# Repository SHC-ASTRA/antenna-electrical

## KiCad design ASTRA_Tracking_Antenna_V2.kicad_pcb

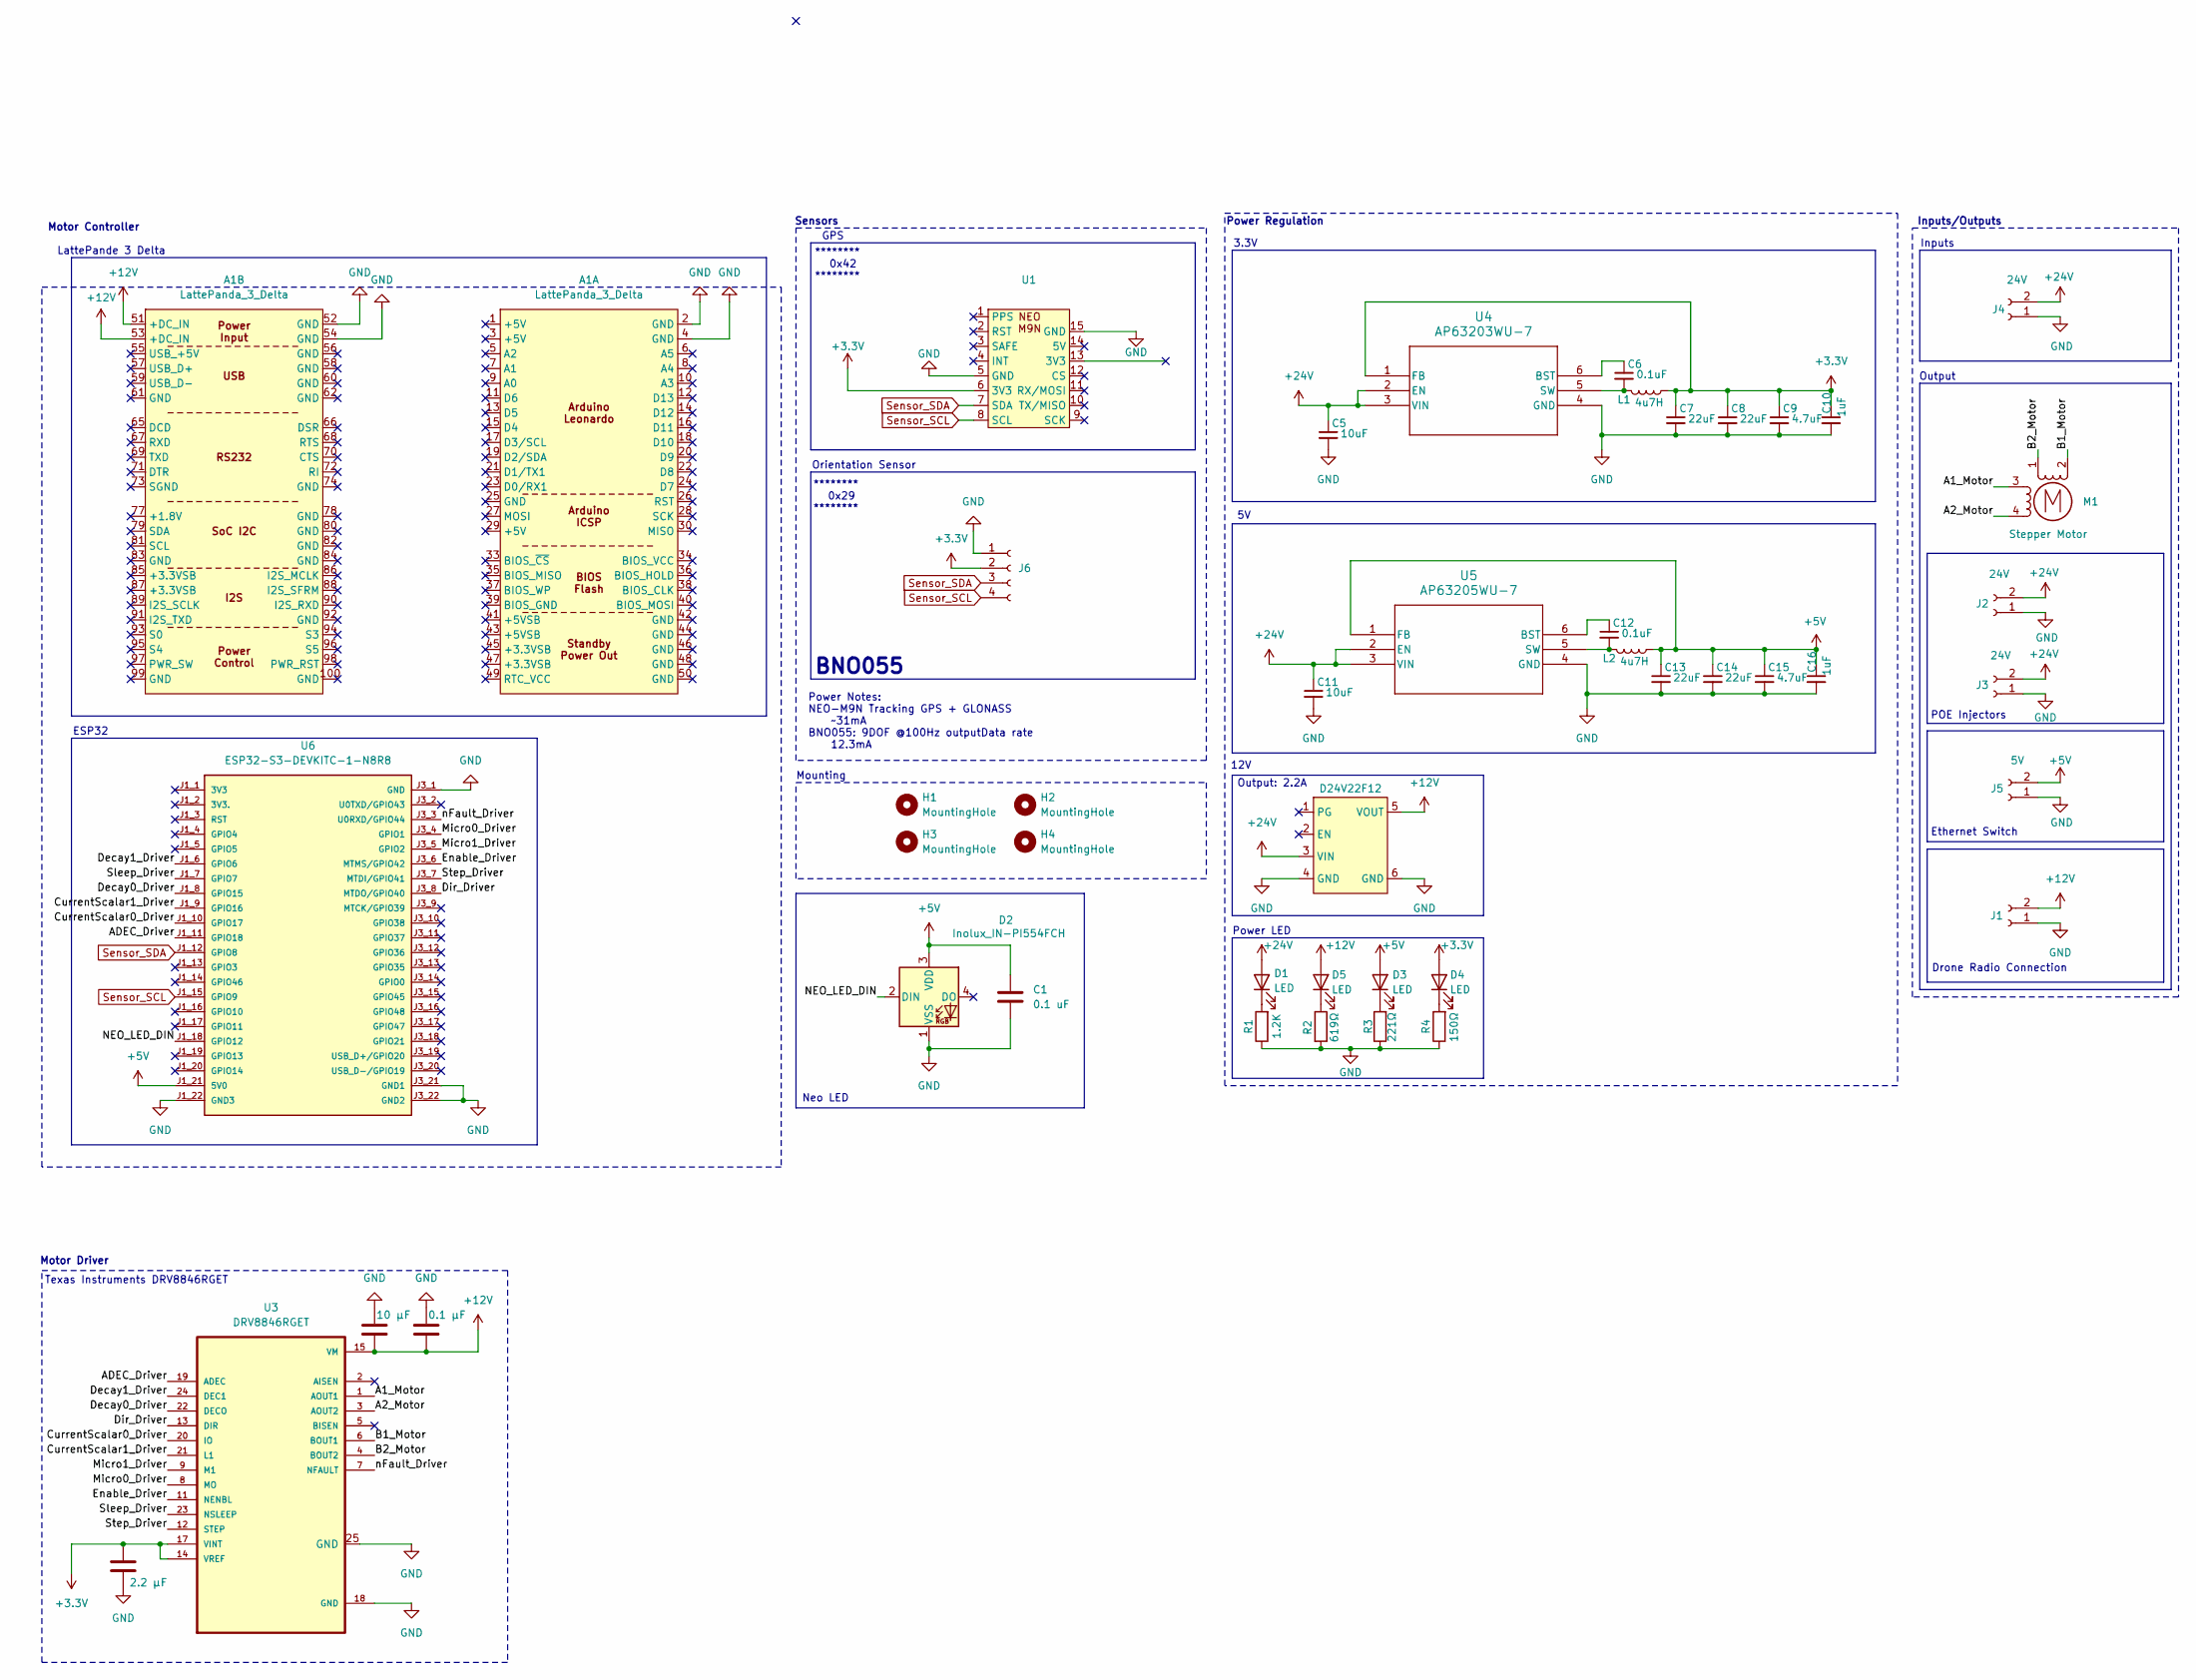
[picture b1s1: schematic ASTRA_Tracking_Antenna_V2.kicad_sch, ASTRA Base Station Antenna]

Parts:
A1: LattePanda_3_Delta
C1: 0.1 uF; C_0603_1608Metric_Pad1.08x0.95mm_HandSolder
C2: 2.2 μF; C_0603_1608Metric_Pad1.08x0.95mm_HandSolder
C3: 10 μF; C_0603_1608Metric_Pad1.08x0.95mm_HandSolder
C4: 0.1 μF; C_0603_1608Metric_Pad1.08x0.95mm_HandSolder
C5, C11: 10uF; C_0603_1608Metric_Pad1.08x0.95mm_HandSolder
C6, C12: 0.1uF; C_0603_1608Metric_Pad1.08x0.95mm_HandSolder
C7, C8, C13, C14: 22uF; C_0603_1608Metric_Pad1.08x0.95mm_HandSolder
C9, C15: 4.7uF; C_0603_1608Metric_Pad1.08x0.95mm_HandSolder
C10, C16: 1uF; C_0603_1608Metric_Pad1.08x0.95mm_HandSolder
D1, D3, D4, D5: LED; LED 3mm
D2: Inolux_IN-PI554FCH; LED_Inolux_IN-PI554FCH_PLCC4_5.0x5.0mm_P3.2mm
H1, H2, H3, H4: MountingHole; 3mm Hole
J1: Conn_01x02_Socket; XT30F_MODIFIED
J2, J3: 24V; XT30F_MODIFIED
J4: 24V; XT60-M
J5: 5V; XT30F_MODIFIED
J6: Conn_01x04_Socket; Molex_Mini-Fit_Jr_5566-04A_2x02_P4.20mm_Vertical
L1, L2: 4u7H; WE-MAPI_4030
M1: Stepper Motor; Molex_Mini-Fit_Jr_5566-04A_2x02_P4.20mm_Vertical
R1: 1.2K; R_0603_1608Metric_Pad0.98x0.95mm_HandSolder
R2: 619Ω; R_0603_1608Metric_Pad0.98x0.95mm_HandSolder
R3: 221Ω; R_0603_1608Metric_Pad0.98x0.95mm_HandSolder
R4: 150Ω; R_0603_1608Metric_Pad0.98x0.95mm_HandSolder
U1: NEO-M9N
U2: D24V22F12; D24V22Fx
U3: DRV8846RGET; DRV8846
U4: AP63203WU-7; SOT95P280X100-6N
U5: AP63205WU-7; SOT95P280X100-6N
U6: ESP32-S3-DEVKITC-1-N8R8

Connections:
+3.3V: C2.1, C7.1, C8.1, C9.1, C10.1, D4.2 (A), J6.2, L1.1, U1.6 (3V3), U3.14 (VREF), U3.17 (VINT), U4.1 (FB)
+5V: C1.1, C13.1, C14.1, C15.1, C16.1, D2.3 (VDD), D3.2 (A), J5.2, L2.1, U5.1 (FB), U6.J1_21 (5V0)
+12V: A1.51 (+DC_IN), A1.53 (+DC_IN), C3.2, C4.2, D5.2 (A), J1.2, U2.5 (VOUT), U3.15 (VM)
+24V: C5.1, C11.1, D1.2 (A), J2.2, J3.2, J4.2, U2.3 (VIN), U4.2 (EN), U4.3 (VIN), U5.2 (EN), U5.3 (VIN)
/A1_Motor: M1.3, U3.1 (AOUT1)
/A2_Motor: M1.4, U3.3 (AOUT2)
/ADEC_Driver: U3.19 (ADEC), U6.J1_11 (GPIO18)
/B1_Motor: M1.2 (-), U3.6 (BOUT1)
/B2_Motor: M1.1, U3.4 (BOUT2)
/CurrentScalar0_Driver: U3.20 (IO), U6.J1_10 (GPIO17)
/CurrentScalar1_Driver: U3.21 (L1), U6.J1_9 (GPIO16)
/Decay0_Driver: U3.22 (DECO), U6.J1_8 (GPIO15)
/Decay1_Driver: U3.24 (DEC1), U6.J1_6 (GPIO6)
/Dir_Driver: U3.13 (DIR), U6.J3_8 (MTDO/GPIO40)
/Enable_Driver: U3.11 (NENBL), U6.J3_6 (MTMS/GPIO42)
/Micro0_Driver: U3.8 (MO), U6.J3_4 (GPIO1)
/Micro1_Driver: U3.9 (M1), U6.J3_5 (GPIO2)
/NEO_LED_DIN: D2.2 (DIN), U6.J1_18 (GPIO12)
/Sleep_Driver: U3.23 (NSLEEP), U6.J1_7 (GPIO7)
/Step_Driver: U3.12 (STEP), U6.J3_7 (MTDI/GPIO41)
/nFault_Driver: U3.7 (NFAULT), U6.J3_3 (U0RXD/GPIO44)
GND: A1.2 (GND), A1.4 (GND), A1.52 (GND), A1.54 (GND), C1.2, C2.2, C3.1, C4.1, C5.2, C7.2, C8.2, C9.2, C10.2, C11.2, C13.2, C14.2, C15.2, C16.2, D2.1 (VSS), J1.1, J2.1, J3.1, J4.1, J5.1, J6.1, R1.1, R2.2, R3.1, R4.1, U1.5 (GND), U1.15 (GND), U2.4 (GND), U2.6 (GND), U3.18 (GND), U3.25 (GND), U4.4 (GND), U5.4 (GND), U6.J1_22 (GND3), U6.J3_1 (GND), U6.J3_21 (GND1), U6.J3_22 (GND2)
unnamed: D1.1 (K), R1.2
unnamed: D3.1 (K), R3.2
unnamed: D4.1 (K), R4.2
unnamed: D5.1 (K), R2.1
unnamed: C6.1, U4.6 (BST)
unnamed: C6.2, L1.2, U4.5 (SW)
unnamed: C12.1, U5.6 (BST)
unnamed: C12.2, L2.2, U5.5 (SW)
Sensor_SCL: J6.4, U1.8 (SCL), U6.J1_15 (GPIO9)
Sensor_SDA: J6.3, U1.7 (SDA), U6.J1_12 (GPIO8)

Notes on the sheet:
Output
Ethernet Switch
Power LED
Drone Radio Connection
12V
POE Injectors
Neo LED
Power Regulation
Inputs/Outputs
Power Notes: NEO-M9N Tracking GPS + GLONASS ~31mA BNO055: 9DOF @100Hz outputData rate 12.3mA
Motor Controller
LattePande 3 Delta
******** 0x42 ********
3.3V
Motor Driver
Texas Instruments DRV8846RGET
ESP32
BNO055
******** 0x29 ********
Mounting
Orientation Sensor
Sensors
GPS
Output: 2.2A
Inputs

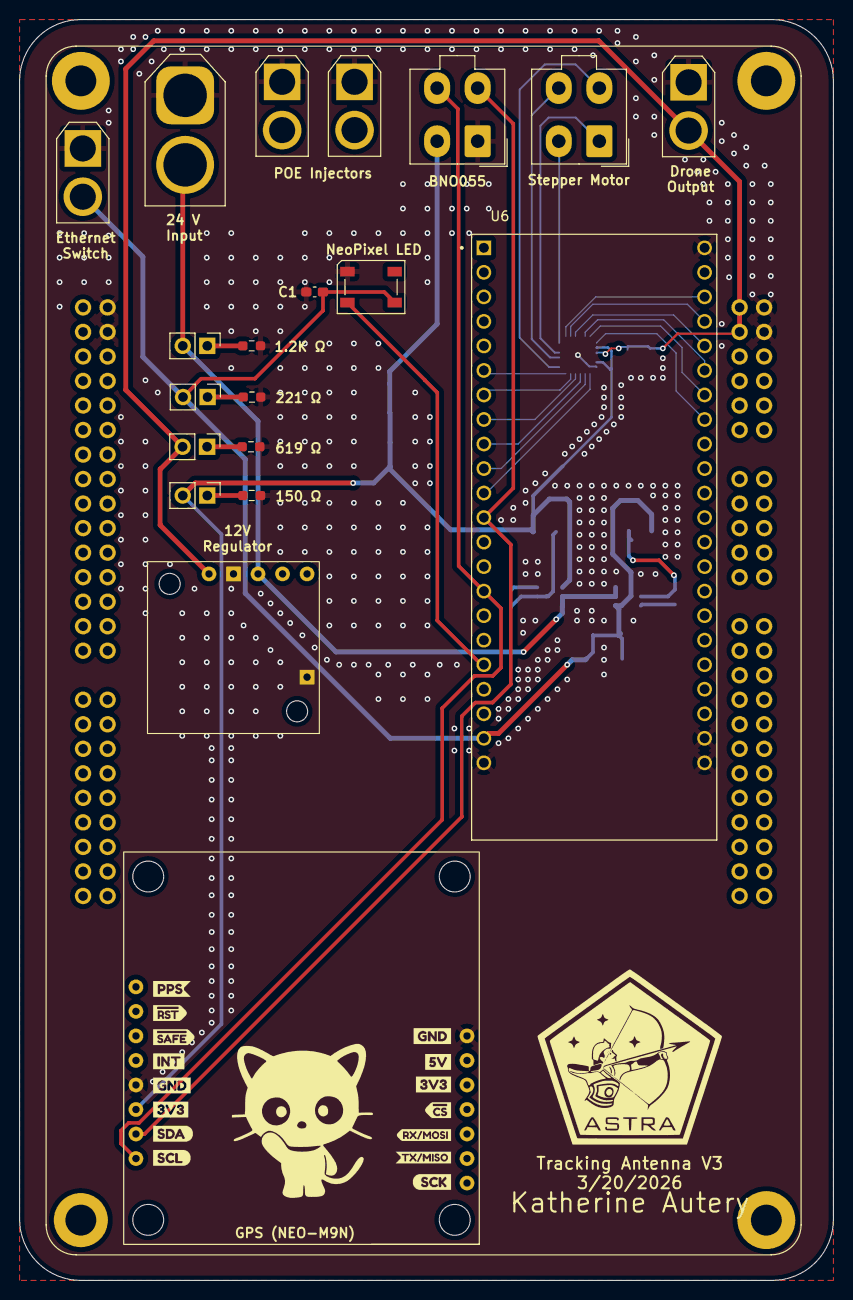
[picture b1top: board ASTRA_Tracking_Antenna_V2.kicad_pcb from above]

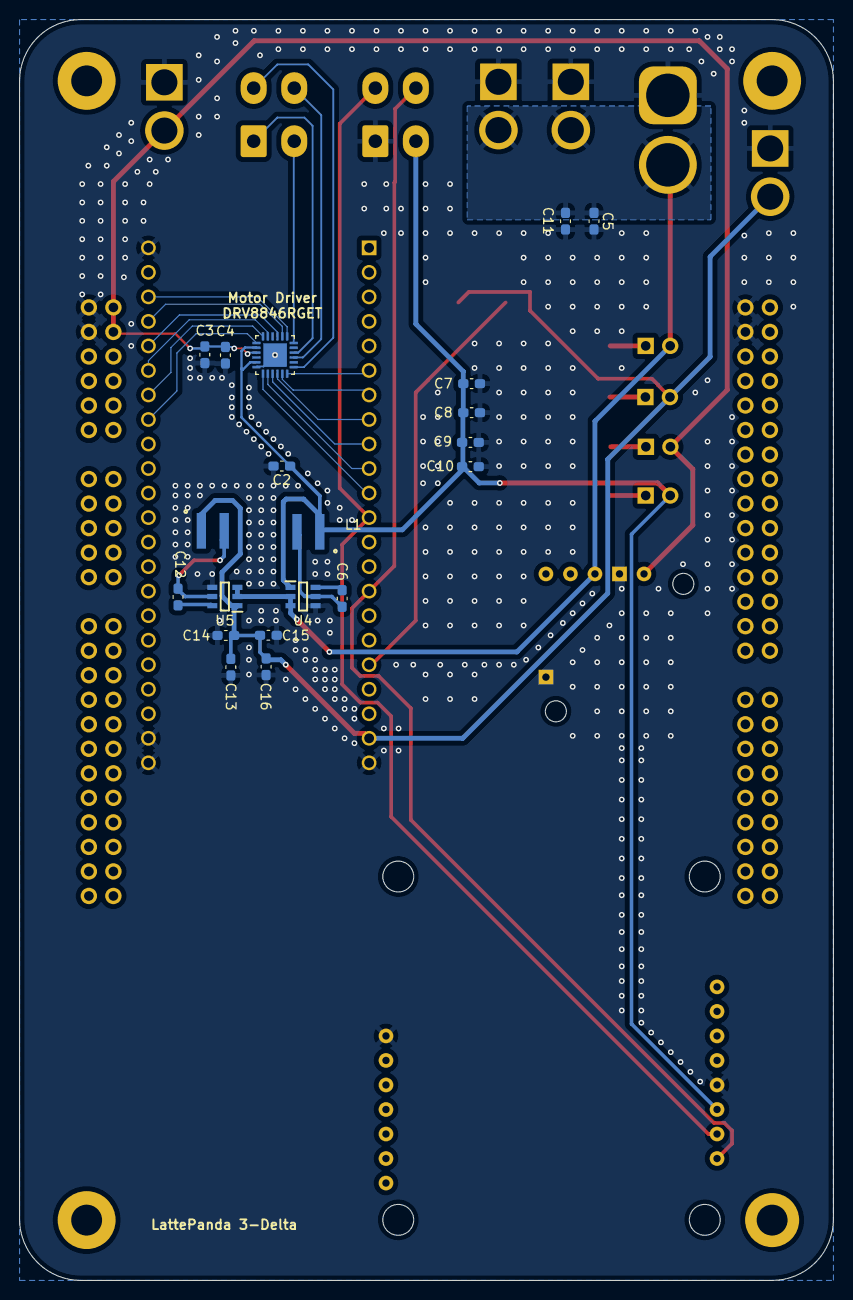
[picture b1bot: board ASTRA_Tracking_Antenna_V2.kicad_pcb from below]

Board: 2 copper layers, 84.3 x 130.6 mm, 41 parts (20 on the bottom side), 32 nets.

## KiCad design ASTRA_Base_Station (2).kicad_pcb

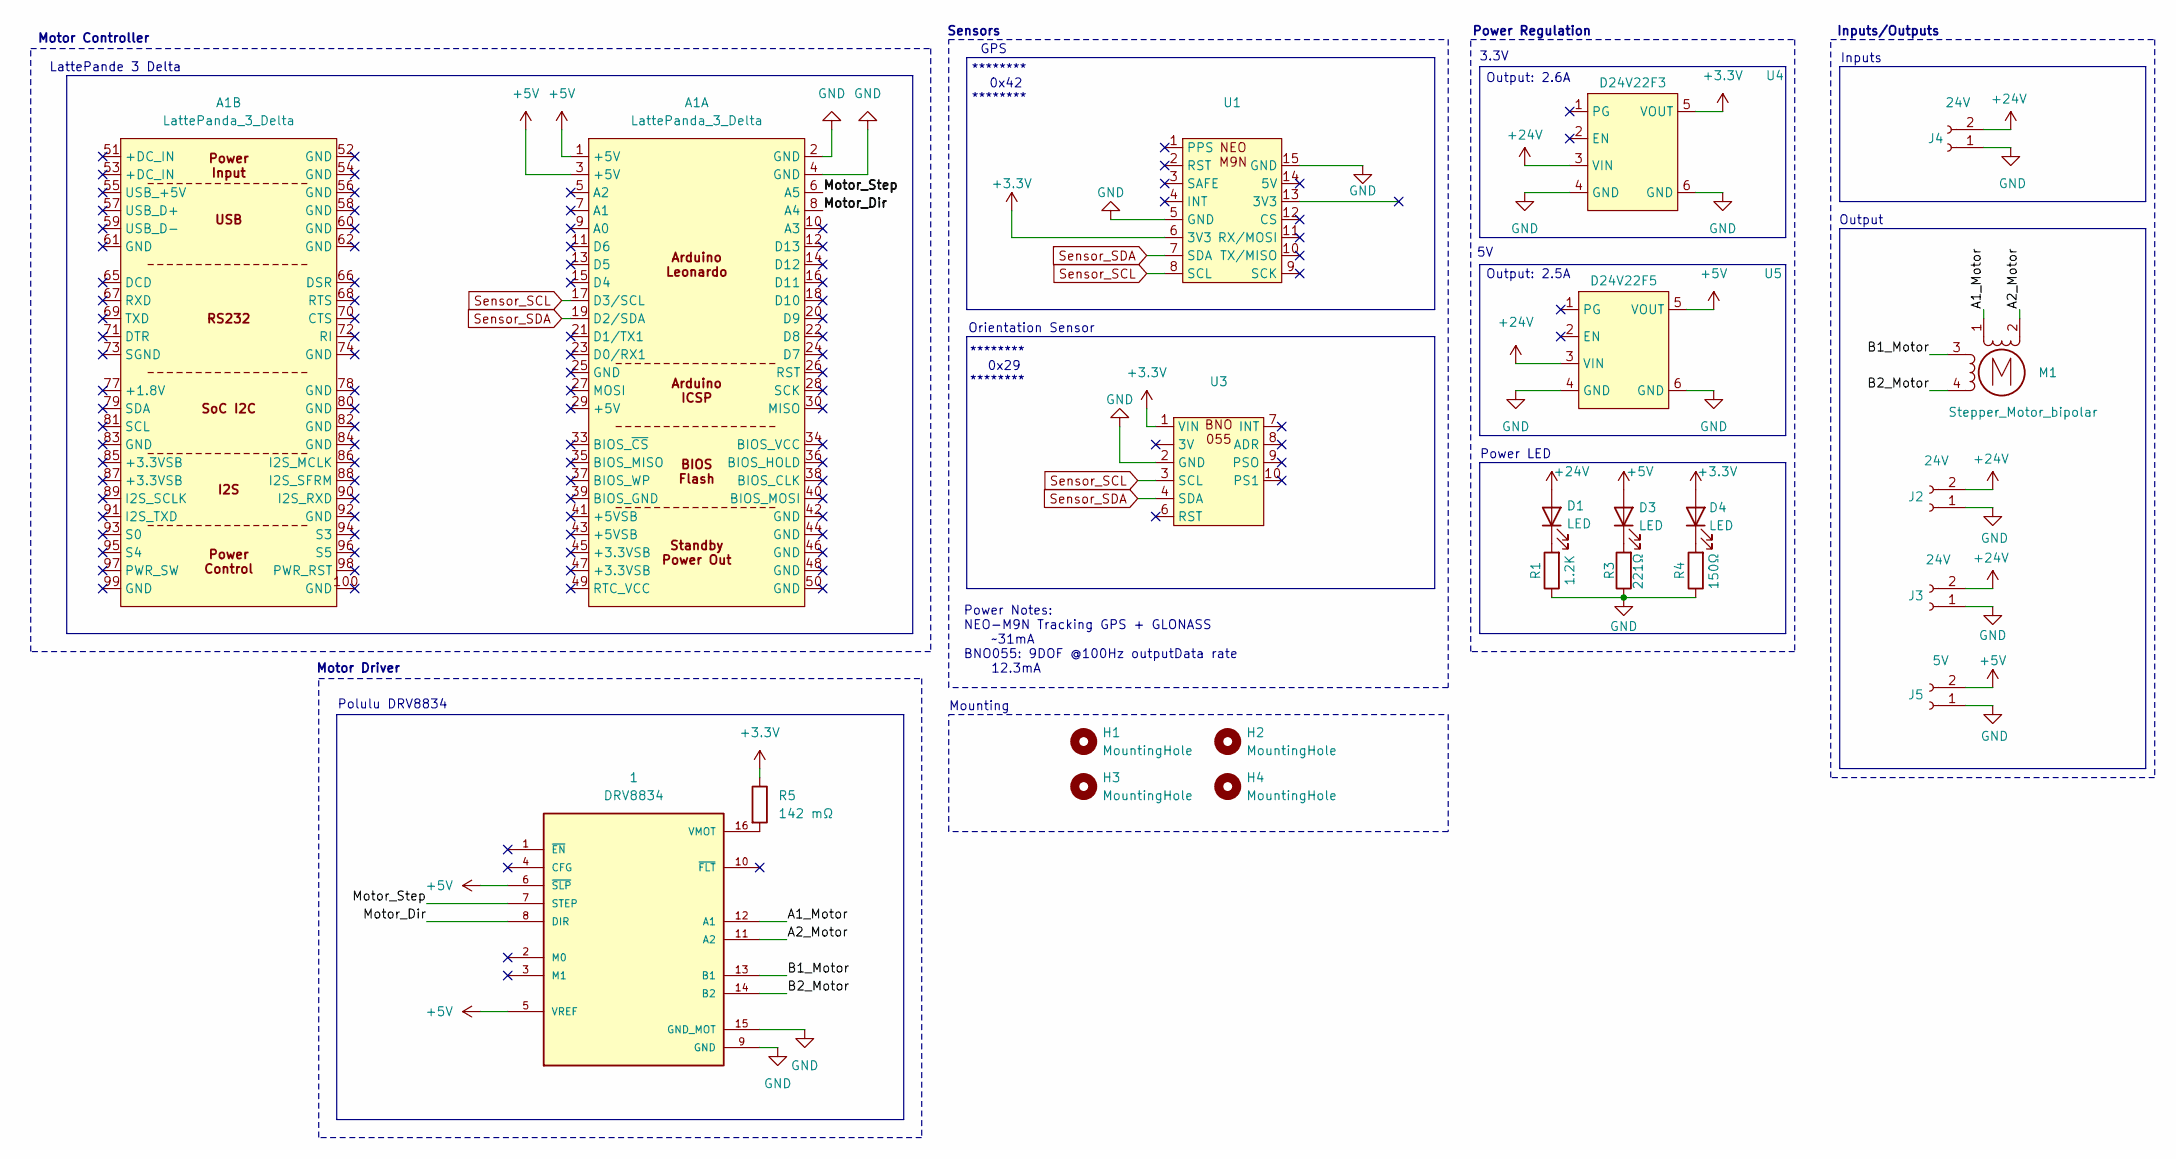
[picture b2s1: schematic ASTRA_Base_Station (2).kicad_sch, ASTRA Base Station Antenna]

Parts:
1: DRV8834; Polulu_DRV8834
A1: LattePanda_3_Delta
D1, D3, D4: LED; LED 3mm
H1, H2, H3, H4: MountingHole; 3mm Hole
J2, J3: 24V; XT30F_MODIFIED
J4: 24V; XT60-M
J5: 5V; XT30F_MODIFIED
M1: Stepper_Motor_bipolar; Molex_Mini-Fit_Jr_5566-04A_2x02_P4.20mm_Vertical
R1: 1.2K; R_0603_1608Metric_Pad0.98x0.95mm_HandSolder
R3: 221Ω; R_0603_1608Metric_Pad0.98x0.95mm_HandSolder
R4: 150Ω; R_0603_1608Metric_Pad0.98x0.95mm_HandSolder
R5: 142 mΩ; R_0603_1608Metric
U1: NEO-M9N
U3: Molex_Mini-Fit_Jr_5566-04A_2x02_P4.20mm_Vertical
U4: D24V22F3; D24V22Fx
U5: D24V22F5; D24V22Fx

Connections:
+3.3V: D4.2 (A), R5.1, U1.6 (3V3), U3.1 (VIN), U4.5 (VOUT)
+5V: 1.5 (VREF), 1.6 (~SLP), A1.1 (+5V), A1.3 (+5V), D3.2 (A), J5.2, U5.5 (VOUT)
+24V: D1.2 (A), J2.2, J3.2, J4.2, U4.3 (VIN), U5.3 (VIN)
/A1_Motor: 1.12 (A1), M1.1
/A2_Motor: 1.11 (A2), M1.2 (-)
/B1_Motor: 1.13 (B1), M1.3
/B2_Motor: 1.14 (B2), M1.4
/Motor_Dir: 1.8 (DIR), A1.8 (A4)
/Motor_Step: 1.7 (STEP), A1.6 (A5)
GND: 1.9 (GND), 1.15 (GND_MOT), A1.2 (GND), A1.4 (GND), J2.1, J3.1, J4.1, J5.1, R1.1, R3.1, R4.1, U1.5 (GND), U1.15 (GND), U3.2 (GND), U4.4 (GND), U4.6 (GND), U5.4 (GND), U5.6 (GND)
unnamed: 1.16 (VMOT), R5.2
unnamed: D1.1 (K), R1.2
unnamed: D3.1 (K), R3.2
unnamed: D4.1 (K), R4.2
Sensor_SCL: A1.17 (D3/SCL), U1.8 (SCL), U3.3 (SCL)
Sensor_SDA: A1.19 (D2/SDA), U1.7 (SDA), U3.4 (SDA)

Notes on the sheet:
Output
Power LED
Power Regulation
Inputs/Outputs
Power Notes: NEO-M9N Tracking GPS + GLONASS ~31mA BNO055: 9DOF @100Hz outputData rate 12.3mA
Motor Controller
LattePande 3 Delta
******** 0x42 ********
Output: 2.5A
Motor Driver
Polulu DRV8834
******** 0x29 ********
Mounting
Orientation Sensor
Output: 2.6A
Sensors
GPS
Inputs
3.3V

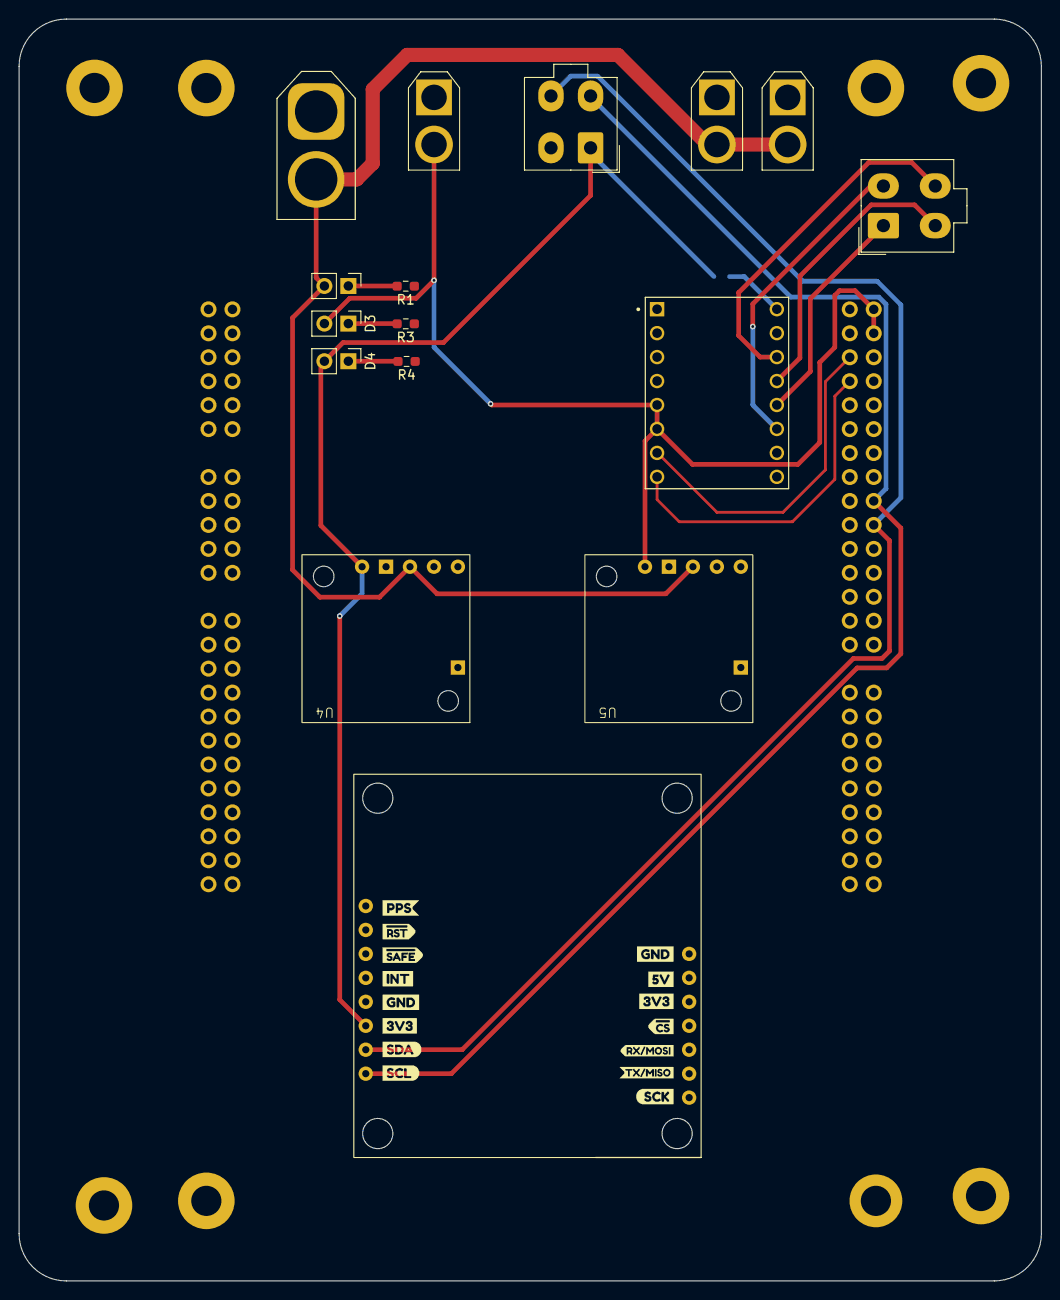
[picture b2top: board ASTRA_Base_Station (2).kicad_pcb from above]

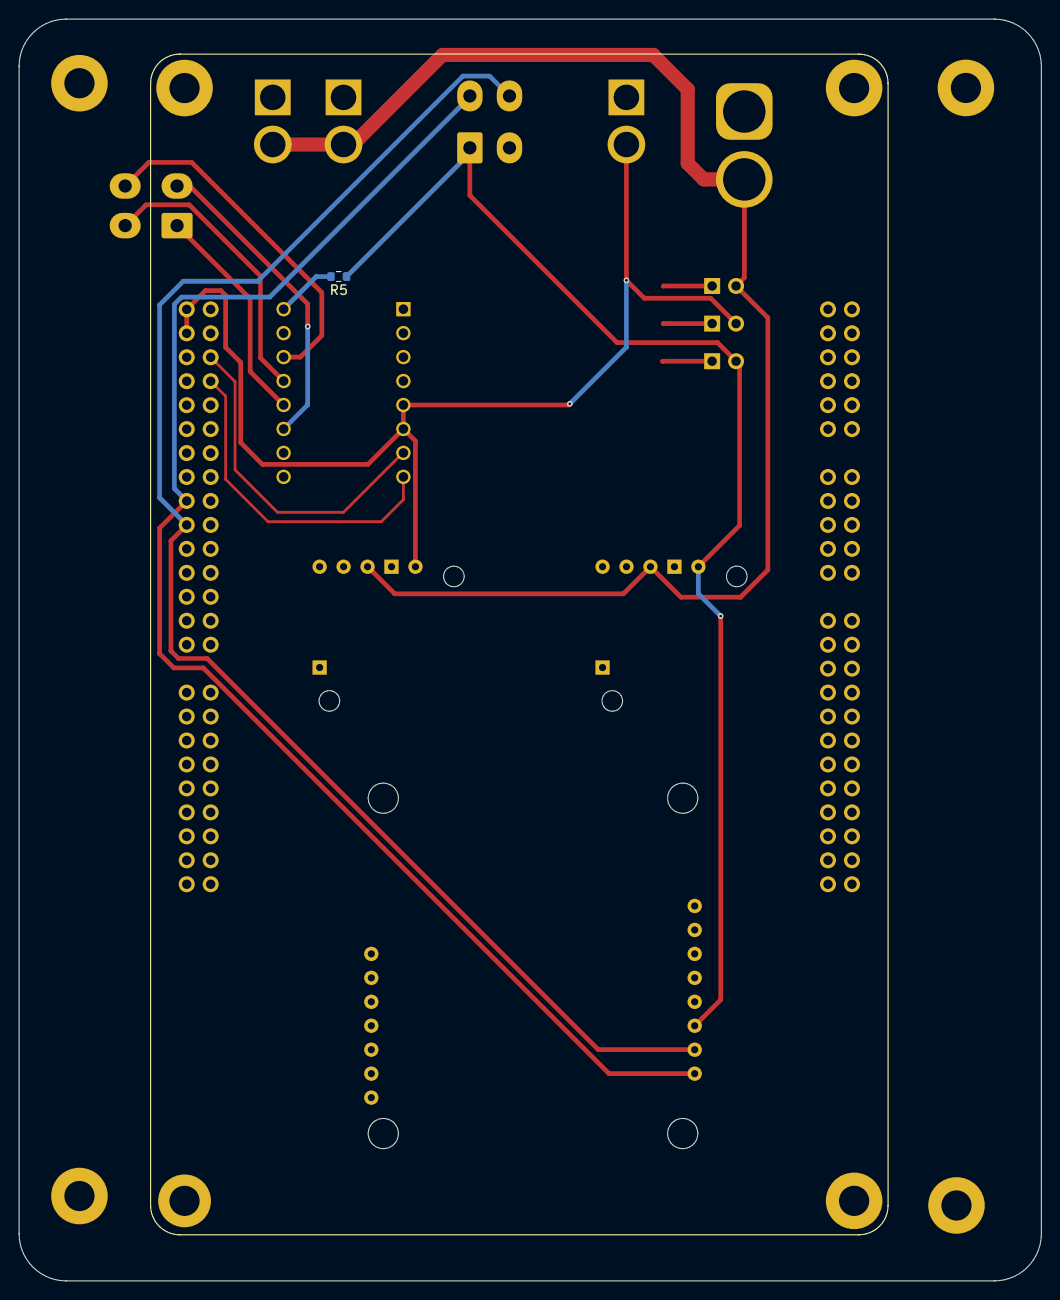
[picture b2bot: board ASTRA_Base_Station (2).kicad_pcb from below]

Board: 2 copper layers, 108.4 x 133.8 mm, 22 parts (2 on the bottom side), 16 nets.

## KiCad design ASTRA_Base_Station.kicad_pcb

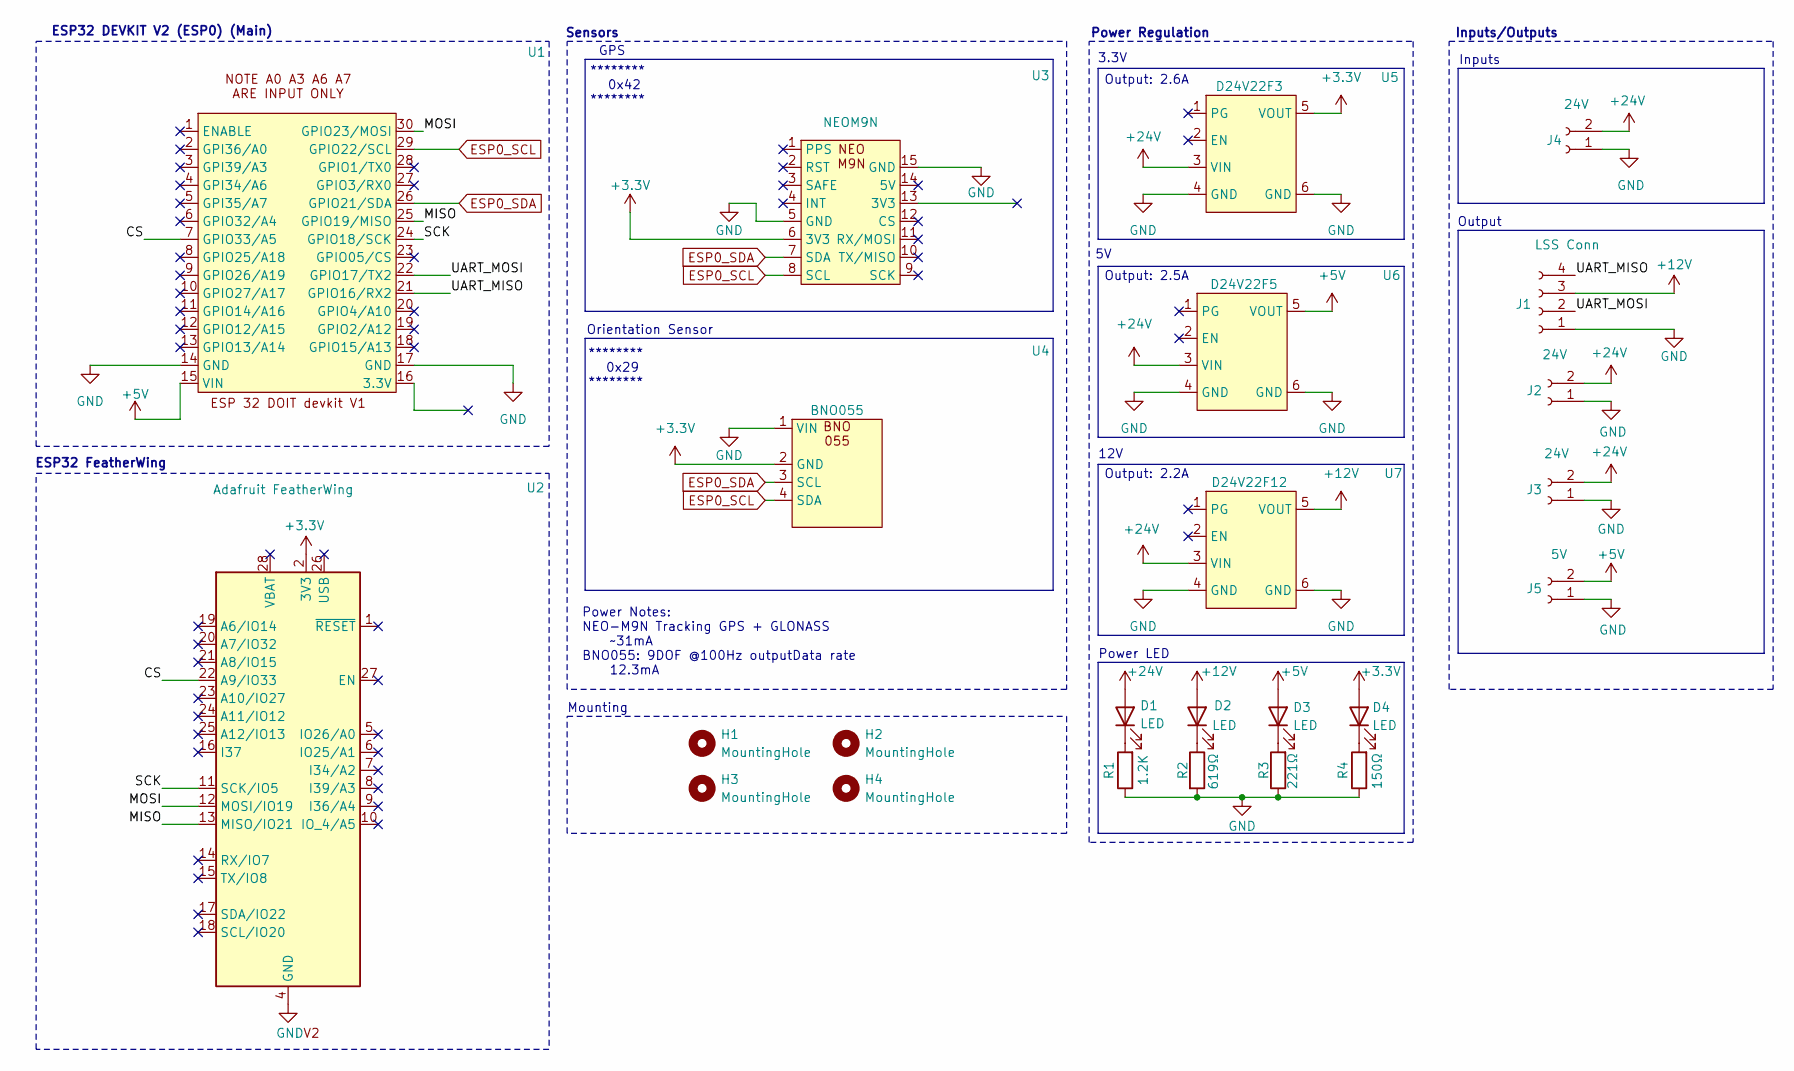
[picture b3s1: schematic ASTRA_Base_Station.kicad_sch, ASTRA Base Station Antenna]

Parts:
D1, D2, D3, D4: LED; LED 3mm
H1, H2, H3, H4: MountingHole; 3mm Hole
J1: LSS Conn; Molex_Mini-Fit_Jr_5566-04A_2x02_P4.20mm_Vertical
J2, J3: 24V; XT30F_MODIFIED
J4: 24V; XT60-M
J5: 5V; XT30F_MODIFIED
R1: 1.2K; R_0603_1608Metric_Pad0.98x0.95mm_HandSolder
R2: 619Ω; R_0603_1608Metric_Pad0.98x0.95mm_HandSolder
R3: 221Ω; R_0603_1608Metric_Pad0.98x0.95mm_HandSolder
R4: 150Ω; R_0603_1608Metric_Pad0.98x0.95mm_HandSolder
U1: esp32_devkit_v1
U2: Adafruit FeatherWing; Adafruit_Feather
U3: NEOM9N; NEO-M9N
U4: BNO055; Molex_Mini-Fit_Jr_5566-04A_2x02_P4.20mm_Vertical
U5: D24V22F3; D24V22Fx
U6: D24V22F5; D24V22Fx
U7: D24V22F12; D24V22Fx

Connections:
+3.3V: D4.2 (A), U2.2 (3V3), U3.6 (3V3), U4.2 (GND), U5.5 (VOUT)
+5V: D3.2 (A), J5.2, U1.15 (VIN), U6.5 (VOUT)
+12V: D2.2 (A), J1.3, U7.5 (VOUT)
+24V: D1.2 (A), J2.2, J3.2, J4.2, U5.3 (VIN), U6.3 (VIN), U7.3 (VIN)
/CS: U1.7 (GPIO33/A5), U2.22 (A9/IO33)
/MISO: U1.25 (GPIO19/MISO), U2.13 (MISO/IO21)
/MOSI: U1.30 (GPIO23/MOSI), U2.12 (MOSI/IO19)
/SCK: U1.24 (GPIO18/SCK), U2.11 (SCK/IO5)
/UART_MISO: J1.4, U1.21 (GPIO16/RX2)
/UART_MOSI: J1.2, U1.22 (GPIO17/TX2)
ESP0_SCL: U1.29 (GPIO22/SCL), U3.8 (SCL), U4.4 (SDA)
ESP0_SDA: U1.26 (GPIO21/SDA), U3.7 (SDA), U4.3 (SCL)
GND: J1.1, J2.1, J3.1, J4.1, J5.1, R1.1, R2.2, R3.1, R4.1, U1.14 (GND), U1.17 (GND), U2.4 (GND), U3.5 (GND), U3.15 (GND), U4.1 (VIN), U5.4 (GND), U5.6 (GND), U6.4 (GND), U6.6 (GND), U7.4 (GND), U7.6 (GND)
unnamed: D1.1 (K), R1.2
unnamed: D2.1 (K), R2.1
unnamed: D3.1 (K), R3.2
unnamed: D4.1 (K), R4.2

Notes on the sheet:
Output
Power LED
12V
Power Regulation
Inputs/Outputs
Power Notes: NEO-M9N Tracking GPS + GLONASS ~31mA BNO055: 9DOF @100Hz outputData rate 12.3mA
ESP32 FeatherWing
******** 0x42 ********
Output: 2.5A
******** 0x29 ********
Mounting
Orientation Sensor
Output: 2.6A
Sensors
GPS
Inputs
3.3V
Output: 2.2A
ESP32 DEVKIT V2 (ESP0) (Main)

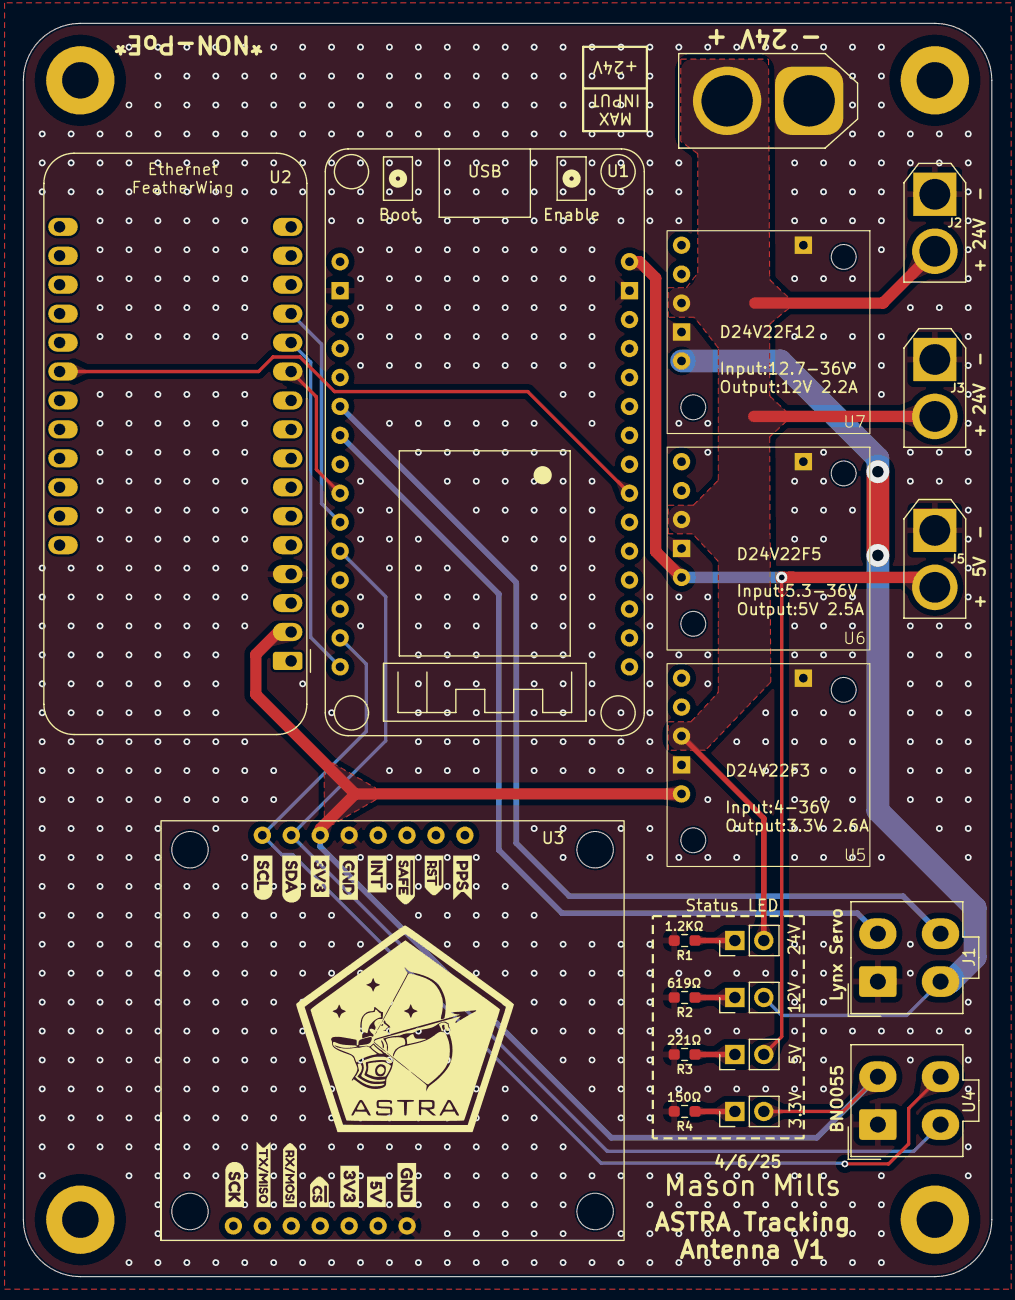
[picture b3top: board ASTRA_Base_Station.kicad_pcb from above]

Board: 2 copper layers, 85.0 x 110.0 mm, 24 parts (0 on the bottom side), 17 nets.

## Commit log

2025-09-11 PCB V1 - Mason Mills - URC 2025 - 04/06/25
2025-10-04 Added Stepper Motor Symbol, Erased Old MC
    Katherine A. added in a symbol for a stepper motor and erased an outdated MC. Next on the agenda is updating the symbol library to be more accurate, adding in the motor driver, and adding all connect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
2025-10-04 Added LattePanda D3
    Added in the symbol for both portions of the LattePanda D3
2025-10-05 LattePanda3D-New-Symbol-Library
    LattePanda D3 was added to the schematic and connected to the sensors. All symbols were updated to a new symbol library contained in the tracking antenna file. New motor and driver left unconnected.
2025-10-09 Added Motor Driver
    Switched the motor driver from the A4988 to the more appropriate DRV8834, added schematic connections to the bipolar stepper motor, updated power regulation, organized schematic sections, and added t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
2025-10-25 PCB Traces Added
    Components have been arranged on the PCB and traces added
    Motor connector needs to be added, ground plane needs to be added, and organization needed.
2025-10-28 Ground Plane Attempt
    Attempted to add a ground plane, it only spawns for some components of the board. Looking into solution.
2025-11-07 PCB Review Draft
    All PCB connections made
2025-12-01 Tracking Antenna PCB V2 Finished
    Tracking Antenna PCB V2 Finished, files renamed for easier understanding
2026-01-06 PCB Created With SMD Driver
    Tracking Antenna PCB revised to incorporate an SMD motor driver, and extraneous files also cleaned up.
2026-01-10 PCB Revisions from Feedback and Drone
    Revisions made to PCB based on feedback, 3.3V Reg swapped, corrections made to motor driver, connector added for drone subteam.
2026-01-22 Silkscreen Addition
    Label added on silkscreen for an output connection
2026-02-07 Final Tracking Antenna V2
    Tracking Antenna final revisions, PCB ordered, drill and gerber files included.
2026-03-30 Tracking Antenna V3
    Tracking Antenna PCB has been revised to orient the LattePanda appropriately and replace previous power regulation system with SMD components
2026-04-01 Tracking Antenna V3 Revisions
    Revisions made to TA PCB from recommendations. MCU switched to newer one, SMD parts shifted around, etc.
2026-04-01 V3 Minor Changes
    Minor part positioning changes.
